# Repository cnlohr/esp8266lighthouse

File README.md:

# esp8266lighthouse

## Project log as of 5/28/17

So, general summary / log for esp8266lighthouse:   It works.  Surprisingly well.

1. If the base station is too close, it the signal quality gets pretty rough.   Too close = 0.8 meters or closer.  This may not be resolvable without a different opamp.  I don't know yet. 
2. There are some corner cases that will cause the ESP to freeze.  This is sad-making, however shouldn't be hard to troubleshoot.
3. The algorithm I'm using to determine frequency seems SLIGHTLY dependent on strength.  When pointed directly at the lighthouse and close, it seems to read slightly high (by about 10-15 kHz)  When at glancing angle or barely visible, it reads spot on.
4. The noise issue due to the ESP is really confusing to me.  Arbitrary moving something or switching power plugs around drastically changes the performance of the system.
5. The ESP8266 will draw ~14mA even in modem-sleep mode all the time if it is monitoring for a lighthouse.  This is sad.  I want to move to an FPGA, but because of the pinout on the ICE40 FPGAs and the fact they never put them in a reasonable package, PCBs for them cost about 10x what normal PCBs cost.
6. Though I can precisely tell frequencies, I cannot simultaneously decode pulses. Each pulse must have about 2uS between them in order to be treated as different pulses.   If we run lighthouses asynchronously, there will be some collisions.  They will need to be ignored.
7. The base stations CAN be run asynchronously and at different rates.  It seems to me that if the lighthouses are operating at the same frequency, they cannot disambiguate asynchronous pulses, but, we should be able to.

## Internal notes:

```
NOTES for transimpedence2/3
TESTS Performed with no C1, TSV992
Making R4 220k instead of 47k seeems to have little effect, but does make it worse.
Switching R1 for 47k just makes it appear drunk. There's some weird feedback thing going on.
    Like it tuned wrong or something.   Making it 10k quiets the signal a lot.
REMOVING C4 no apparent impact.

R5=10k, C5=10p -> R5=4.7k, C5=18p =>> Improvement.
Adding C1=1pF decreases amplitude a little bit but also cleans up edges.
Removing C6 seems to reduce amplitude slightly.

Far peak:
C1 none C6 none => .1238V noise, .998V Far Light
C1 none C6 1pF    => .1238V noise, .498V Far Light
C1 1pF  C6 none => .1135V noise, .358V Far Light
C1 1pF C6 1pF     => .087V Noise, .202V Far Light

Recommendation: Remove C6, C1.

Out of the following op amps...
TSH82, TSV992, AD8052, TSH22, TSH462,
TSV992 demolished.

Useful photodiodes:
PART / NOISE / FAR / Cost
PD70-01C/TR7:  .159 / .418 / .47
PD438C: .237 / .550 / .39
QSD2030F: .216 / .5363 / .30
BPW34/S-Z: .283 / .6345 /.497
PD15-216/TR8: UNUSABLE
VBPW34FAS: .175 / .815 / .778
VBPW34FASR: .2631 / .644 / .778
BPW34: .237 / .577 / .62
PD15-22C/TR8: Unworkable.
PD15-22B/TR8: Unworkable.
PD70-TR10: .2063 / .4024 / .41
BPW46: .247 / .968 / .61

Winners: BPW46, BPW34/S-Z, BPW34FAS + VBPW34FASR
Major Winners: BPW46/VBPW34FAS
```

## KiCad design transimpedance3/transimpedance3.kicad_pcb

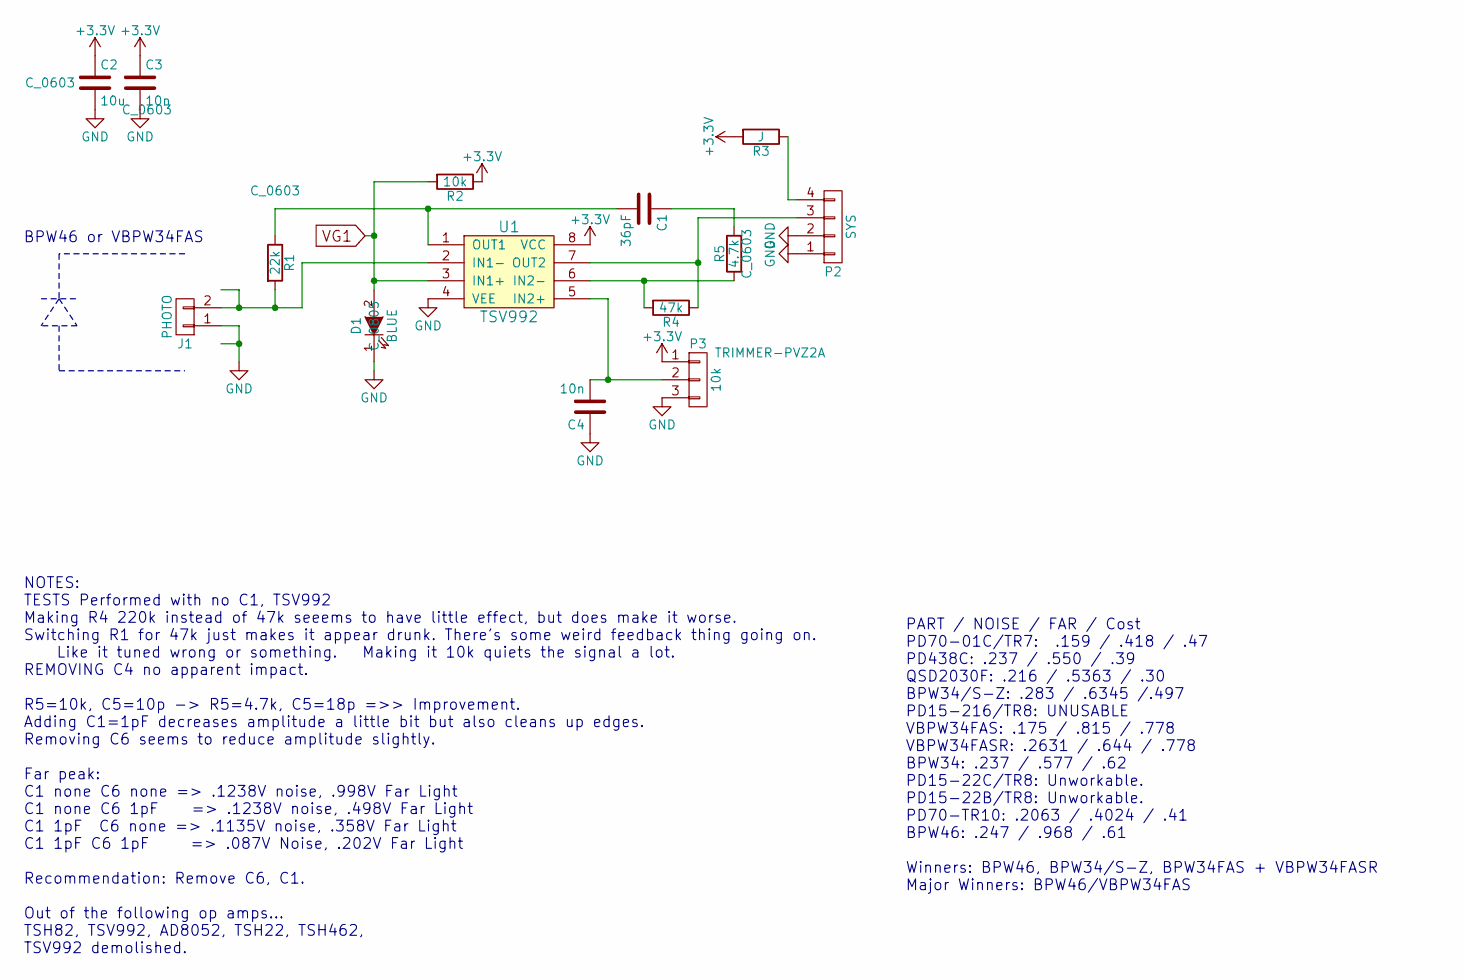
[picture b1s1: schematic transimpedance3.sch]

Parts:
C1: 36pF; C_0603
C2: 10u; C_0603
C3, C4: 10n; C_0603
D1: BLUE; C_0805
J1: PHOTO; Pin_Header_Straight_1x02_Pitch2.54mm
P2: SYS; TerminalBlock_Pheonix_MPT-2.54mm_4pol
P3: 10k; TRIMMER-PVZ2A
R1: 22k; C_0603
R2: 10k; C_0603
R3: J; C_0603
R4: 47k; C_0603
R5: 4.7k; C_0603
U1: TSV992; SSOP-8_2.95x2.8mm_Pitch0.65mm

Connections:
+3V3: C2.1, C3.1, P3.1, R2.1, R3.2, U1.8 (VCC)
GND: C2.2, C3.2, C4.1, D1.1 (K), J1.1, P2.1, P2.2, P3.3, U1.4 (VEE)
unnamed: C1.1, R5.2
unnamed: C1.2, R1.1, U1.1 (OUT1)
unnamed: C4.2, P3.2, U1.5 (IN2+)
unnamed: J1.2, R1.2, U1.2 (IN1-)
unnamed: P2.3, R4.1, U1.7 (OUT2)
unnamed: P2.4, R3.1
unnamed: R4.2, R5.1, U1.6 (IN2-)
VG1: D1.2 (A), R2.2, U1.3 (IN1+)

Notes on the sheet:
NOTES: TESTS Performed with no C1, TSV992 Making R4 220k instead of 47k seeems to have little effect, but does make it worse. Switching R1 for 47k just makes it appear drunk. There's some weird feedback thing going on. Like it tuned wrong or something. Making it 10k quiets the signal a lot. REMOVIN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
PART / NOISE / FAR / Cost PD70-01C/TR7: .159 / .418 / .47 PD438C: .237 / .550 / .39 QSD2030F: .216 / .5363 / .30 BPW34/S-Z: .283 / .6345 /.497 PD15-216/TR8: UNUSABLE VBPW34FAS: .175 / .815 / .778 VBPW34FASR: .2631 / .644 / .778 BPW34: .237 / .577 / .62 PD15-22C/TR8: Unworkable. PD15-22B/TR8: Unwork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
BPW46 or VBPW34FAS

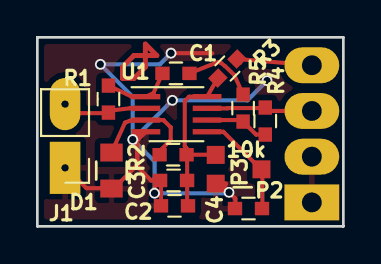
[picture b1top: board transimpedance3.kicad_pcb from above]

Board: 2 copper layers, 17.0 x 10.5 mm, 14 parts (0 on the bottom side), 10 nets.

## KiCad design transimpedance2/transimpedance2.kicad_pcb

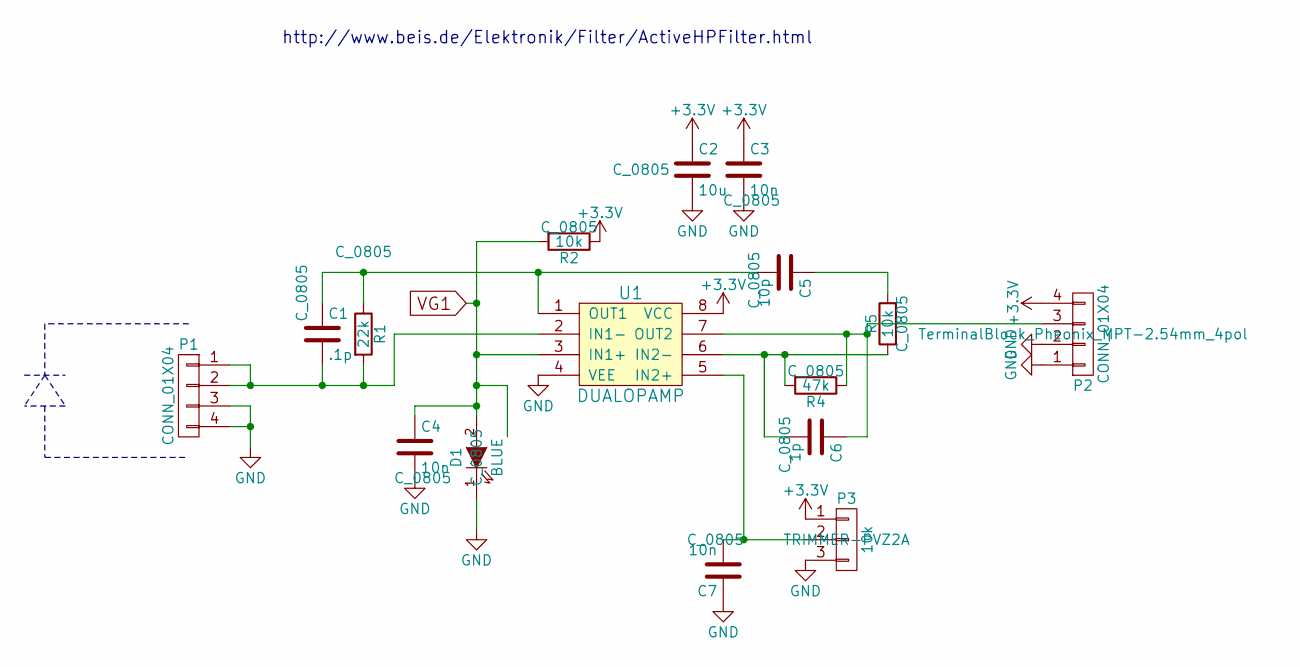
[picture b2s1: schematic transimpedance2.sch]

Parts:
C1: .1p; C_0805
C2: 10u; C_0805
C3, C4, C7: 10n; C_0805
C5: 10p; C_0805
C6: 1p; C_0805
D1: BLUE; C_0805
P1, P2: CONN_01X04; TerminalBlock_Pheonix_MPT-2.54mm_4pol
P3: 10k; TRIMMER-PVZ2A
R1: 22k; C_0805
R2, R5: 10k; C_0805
R4: 47k; C_0805
U1: DUALOPAMP; SOIC-8_3.9x4.9mm_Pitch1.27mm

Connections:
+3V3: C2.1, C3.1, P2.4, P3.1, R2.1, U1.8 (VCC)
GND: C2.2, C3.2, C4.2, C7.1, D1.1 (K), P1.3, P1.4, P2.1, P2.2, P3.3, U1.4 (VEE)
unnamed: C1.1, C5.2, R1.1, U1.1 (OUT1)
unnamed: C1.2, P1.1, P1.2, R1.2, U1.2 (IN1-)
unnamed: C5.1, R5.2
unnamed: C6.1, P2.3, R4.1, U1.7 (OUT2)
unnamed: C6.2, R4.2, R5.1, U1.6 (IN2-)
unnamed: C7.2, P3.2, U1.5 (IN2+)
VG1: C4.1, D1.2 (A), R2.2, U1.3 (IN1+)

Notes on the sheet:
http://www.beis.de/Elektronik/Filter/ActiveHPFilter.html

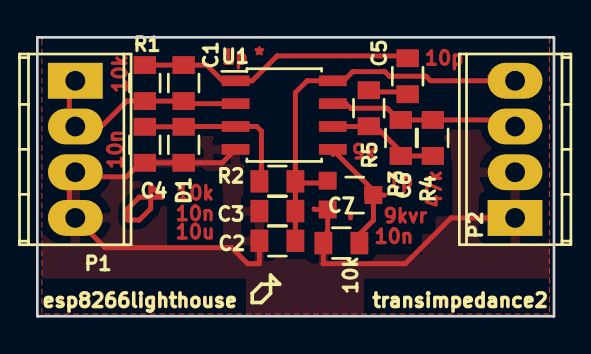
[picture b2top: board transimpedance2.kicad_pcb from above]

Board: 2 copper layers, 28.7 x 15.5 mm, 16 parts (0 on the bottom side), 9 nets.

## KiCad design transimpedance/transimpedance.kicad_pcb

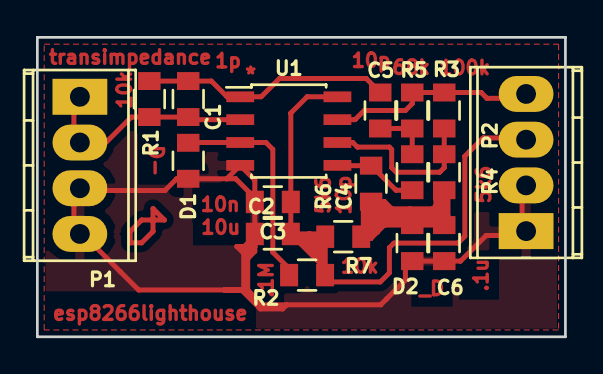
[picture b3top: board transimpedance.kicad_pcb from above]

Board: 2 copper layers, 29.3 x 16.6 mm, 18 parts (0 on the bottom side), 10 nets.

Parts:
C1, C4, C5: 10p; C_0805
C2: 10u; C_0805
C3: 10n; C_0805
C6: 100n; C_0805
D1, D2: BLUE; C_0805
P1, P2: CONN_01X04; TerminalBlock_Pheonix_MPT-2.54mm_4pol
R1, R7: 10k; C_0805
R2: 100k; C_0805
R3: 106k; C_0805
R4, R6: 5.6k; C_0805
R5: 68k; C_0805
U1: DUALOPAMP; SOIC-8_3.9x4.9mm_Pitch1.27mm

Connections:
+3V3: C2.1, C3.1, P2.3, R2.1, R7.1, U1.8
GND: C2.2, C3.2, C6.2, D1.1, D2.1, P1.3, P1.4, P2.1, P2.2, U1.4
unnamed: C1.1, C5.1, R1.1, U1.1
unnamed: C1.2, P1.1, P1.2, R1.2, U1.2
unnamed: C4.1, C5.2, R5.1
unnamed: C4.2, R6.2, U1.5
unnamed: P2.4, R3.2, R5.2, U1.7
unnamed: R3.1, R4.2, U1.6
VG1: D1.2, R2.2, U1.3
VGND: C6.1, D2.2, R4.1, R6.1, R7.2

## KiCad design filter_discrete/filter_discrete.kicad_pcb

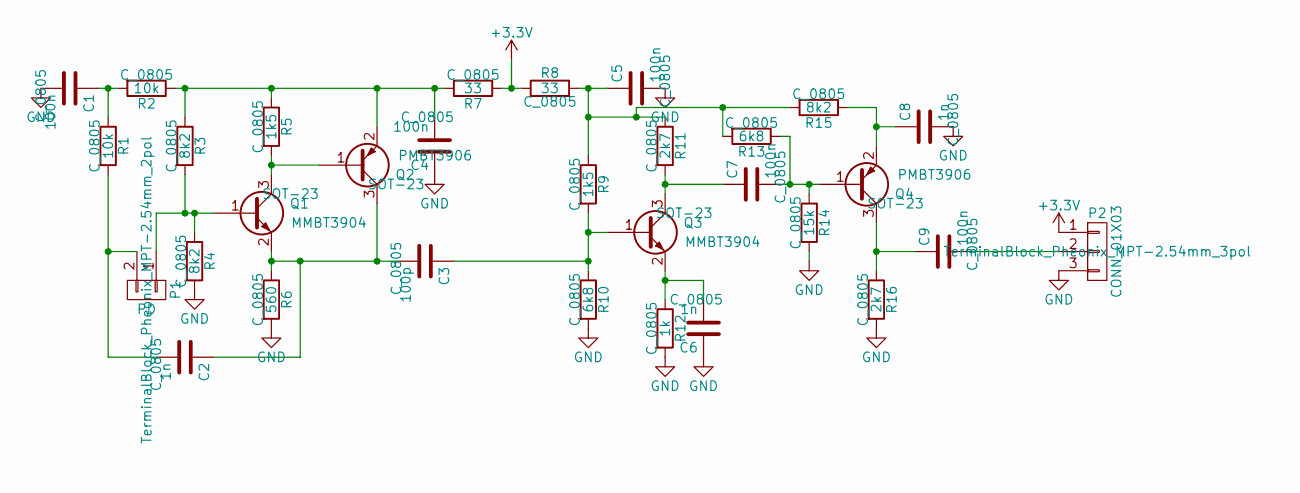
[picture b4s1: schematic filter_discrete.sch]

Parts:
C1, C4, C5, C7, C9: 100n; C_0805
C2, C6, C8: 1n; C_0805
C3: 100p; C_0805
P1: PD; TerminalBlock_Pheonix_MPT-2.54mm_2pol
P2: CONN_01X03; TerminalBlock_Pheonix_MPT-2.54mm_3pol
Q1, Q3: MMBT3904; SOT-23
Q2, Q4: PMBT3906; SOT-23
R1, R2: 10k; C_0805
R3, R4, R15: 8k2; C_0805
R5, R9: 1k5; C_0805
R6: 560; C_0805
R7, R8: 33; C_0805
R10, R13: 6k8; C_0805
R11, R16: 2k7; C_0805
R12: 1k; C_0805
R14: 15k; C_0805

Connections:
+3V3: P2.1, R7.1, R8.1
GND: C1.2, C4.1, C5.2, C6.1, C8.2, P2.3, R4.2, R6.2, R10.2, R12.2, R14.2, R16.2
unnamed: C1.1, R1.1, R2.2
unnamed: C2.1, C3.2, Q1.2 (E), Q2.3 (C), R6.1
unnamed: C2.2, P1.2, R1.2
unnamed: C3.1, Q3.1 (B), R9.2, R10.1
unnamed: C4.2, Q2.2 (E), R2.1, R3.1, R5.1, R7.2
unnamed: C5.1, R8.2, R9.1, R11.1, R13.2, R15.2
unnamed: C6.2, Q3.2 (E), R12.1
unnamed: C7.1, Q3.3 (C), R11.2
unnamed: C7.2, Q4.1 (B), R13.1, R14.1
unnamed: C8.1, Q4.2 (E), R15.1
unnamed: C9.1, Q4.3 (C), R16.1
unnamed: C9.2, P2.2
unnamed: P1.1, Q1.1 (B), R3.2, R4.1
unnamed: Q1.3 (C), Q2.1 (B), R5.2

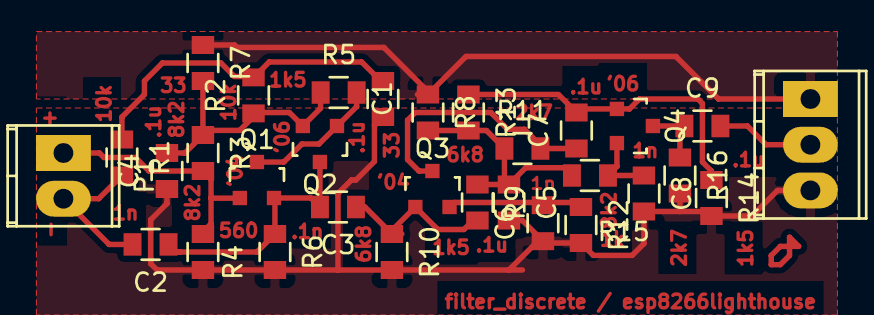
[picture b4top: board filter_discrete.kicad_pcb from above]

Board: 2 copper layers, 31 parts (0 on the bottom side), 16 nets.

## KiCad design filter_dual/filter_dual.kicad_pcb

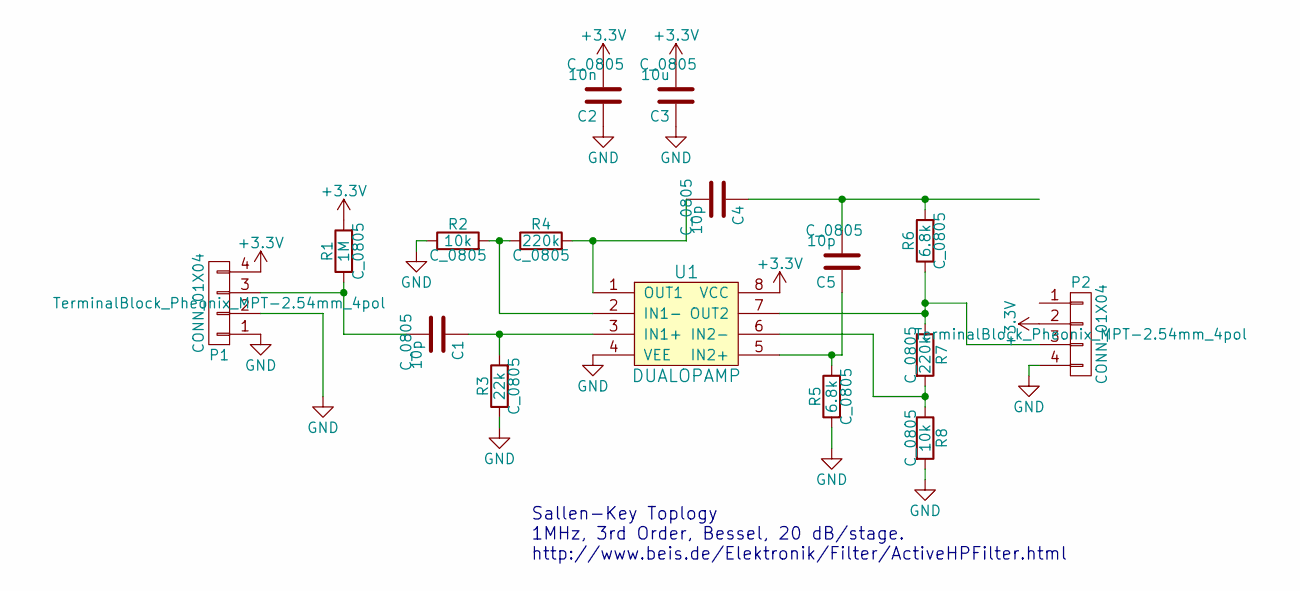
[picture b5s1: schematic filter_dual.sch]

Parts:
C1, C4, C5: 10p; C_0805
C2: 10n; C_0805
C3: 10u; C_0805
P1, P2: CONN_01X04; TerminalBlock_Pheonix_MPT-2.54mm_4pol
R1: 1M; C_0805
R2, R8: 10k; C_0805
R3: 22k; C_0805
R4, R7: 220k; C_0805
R5, R6: 6.8k; C_0805
U1: DUALOPAMP; SOIC-8_3.9x4.9mm_Pitch1.27mm

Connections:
+3V3: C2.2, C3.2, P1.4, P2.2, R1.2, U1.8 (VCC)
GND: C2.1, C3.1, P1.1, P1.2, P2.4, R2.1, R3.1, R5.1, R8.2, U1.4 (VEE)
unnamed: C1.1, R3.2, U1.3 (IN1+)
unnamed: C1.2, P1.3, R1.1
unnamed: C4.1, C5.2, R6.2
unnamed: C4.2, R4.2, U1.1 (OUT1)
unnamed: C5.1, R5.2, U1.5 (IN2+)
unnamed: P2.3, R6.1, R7.1, U1.7 (OUT2)
unnamed: R2.2, R4.1, U1.2 (IN1-)
unnamed: R7.2, R8.1, U1.6 (IN2-)

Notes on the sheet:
Sallen-Key Toplogy 1MHz, 3rd Order, Bessel, 20 dB/stage. http://www.beis.de/Elektronik/Filter/ActiveHPFilter.html

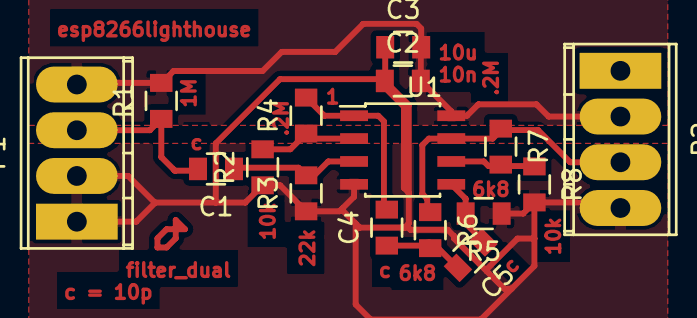
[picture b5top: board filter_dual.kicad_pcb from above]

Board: 2 copper layers, 16 parts (0 on the bottom side), 10 nets.

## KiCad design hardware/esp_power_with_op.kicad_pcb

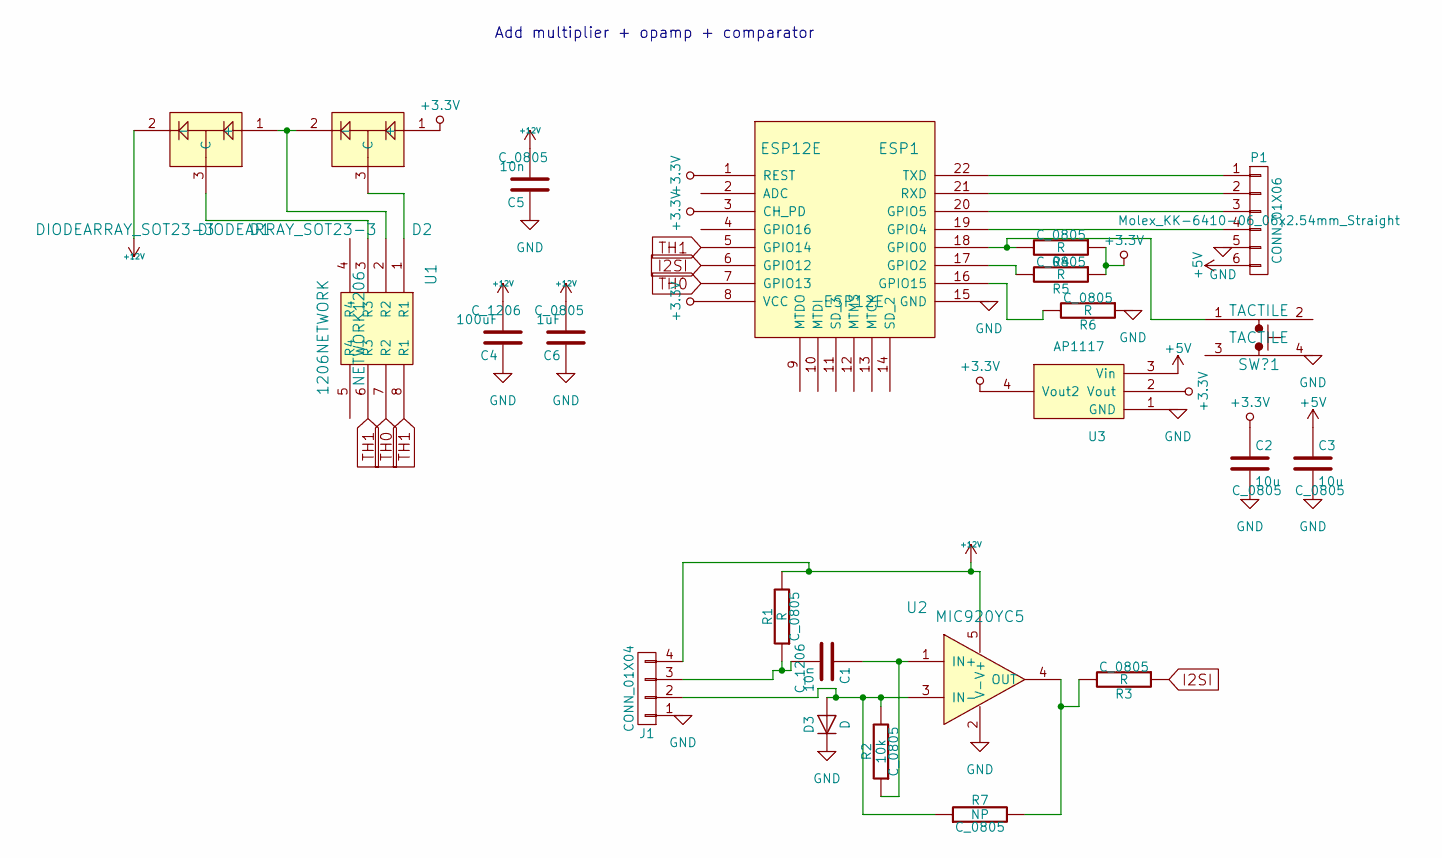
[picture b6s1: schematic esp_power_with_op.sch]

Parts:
C1: 10n; C_1206
C2, C3: 10u; C_0805
C4: 100uF; C_1206
C5: 10n; C_0805
C6: 1uF; C_0805
D1, D2: DIODEARRAY_SOT23-3; SOT-23
D3: D; C_1206
ESP1: ESP12E
J1: CONN_01X04; Molex_KK-6410-04_04x2.54mm_Straight
P1: CONN_01X06; Molex_KK-6410-06_06x2.54mm_Straight
R1, R3, R4, R5, R6: R; C_0805
R2: 10k; C_0805
R7: NP; C_0805
SW?1: TACTILE
U1: 1206NETWORK; NETWORK1206
U2: MIC920YC5; SOT-353_SC-70-5
U3: AP1117; SOT-223

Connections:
+3.3V: C2.1, D2.1 (+), ESP1.1 (REST), ESP1.3 (CH_PD), ESP1.8 (VCC), R4.1, R5.1, U3.2 (Vout), U3.4 (Vout2)
+5V: C3.1, P1.6, U3.3 (Vin)
+12V: C4.2, C5.2, C6.2, D1.2 (-), J1.4, R1.2, U2.5 (V+)
GND: C2.2, C3.2, C4.1, C5.1, C6.1, D3.1 (K), ESP1.15 (GND), J1.1, P1.5, R6.1, SW?1.4, U2.2 (V-), U3.1 (GND)
I2SI: ESP1.6 (GPIO12), R3.1
unnamed: C1.1, R2.1, U2.1 (IN+)
unnamed: C1.2, J1.3, R1.1
unnamed: D1.1 (+), D2.2 (-), U1.2 (R2)
unnamed: D1.3 (C), U1.3 (R3)
unnamed: D2.3 (C), U1.1 (R1)
unnamed: D3.2 (A), J1.2, R2.2, R7.1, U2.3 (IN-)
unnamed: ESP1.16 (GPIO15), R6.2
unnamed: ESP1.17 (GPIO2), R5.2
unnamed: ESP1.18 (GPIO0), R4.2, SW?1.1
unnamed: ESP1.19 (GPIO4), P1.4
unnamed: ESP1.20 (GPIO5), P1.3
unnamed: ESP1.21 (RXD), P1.2
unnamed: ESP1.22 (TXD), P1.1
unnamed: R3.2, R7.2, U2.4 (OUT)
TH0: ESP1.7 (GPIO13), U1.7 (R2)
TH1: ESP1.5 (GPIO14), U1.6 (R3), U1.8 (R1)

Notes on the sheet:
Add multiplier + opamp + comparator

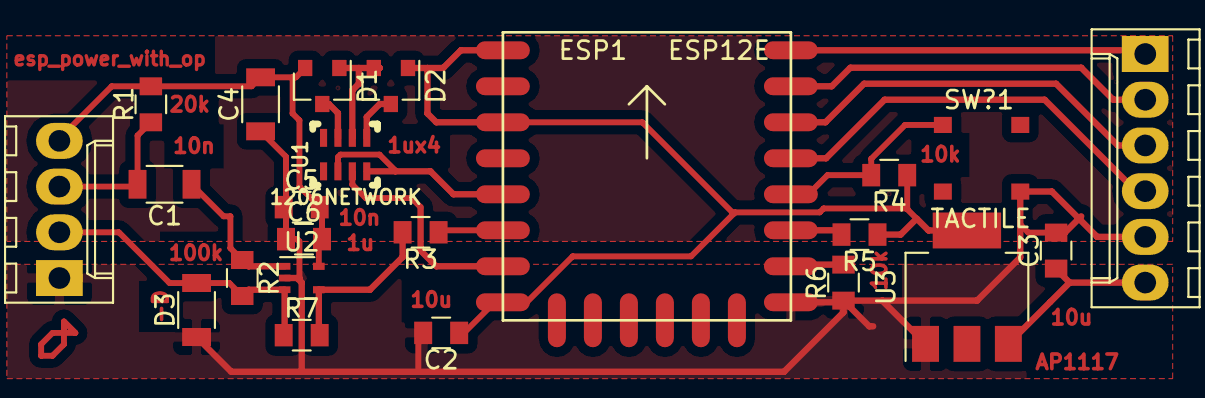
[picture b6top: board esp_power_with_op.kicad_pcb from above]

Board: 2 copper layers, 23 parts (0 on the bottom side), 21 nets.

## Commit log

2017-03-26 Add all parts to this repo.
2017-03-26 remove chage pump etc
2017-03-26 Update - swapping files aroundo
2017-03-30 Add other filters.
2017-03-30 add updated files
2017-03-30 update lighthouse designs
2017-03-31 update transimpedence filter.
2017-04-04 update with transimpedance 2
2017-05-01 update the transimpedance esign.
2017-05-11 update transimpedance3
2017-05-11 update tia3
2017-05-12 Update all designs with newest to fab.
2017-05-12 update schematic
2017-05-15 Update the esp8266 lighthouse code to allow browser-interaction.
2017-05-15 Update firmware, and improve performance.
2017-05-15 cleanup styles on website, plus, remove the I2S TX engine. Hopefully this will relieve some DMA contention.
2017-05-16 bump submodule
2017-05-16 added missing unit
    Browsers only allow this in quirks mode and you shouldn't rely on that.
    I know it's nothing major, just noticed it in the steam ^^
2017-05-17 Update to a binary websockets. Improve usage
2017-05-18 Update processing systems
2017-05-18 Closing in on a solution!!!
2017-05-18 Working successfully with web gui (Also update project for kicad)
2017-05-18 Update with fully functional tracking code and sending over UDP (though there is some debt that need be handled)
2017-05-18 Issues with the DMA buffer system in the ESP. Must be fixed. Other than that, getting very close.
2017-05-18 fix bug with bad scoping.
2017-05-19 Getting very close. A few buffer underruns and I need to stop using UDP (for now!)
2017-05-19 oops, shouldn't have deleted that code from the custom controller
2017-05-27 Transition over to TCP for main transport mechanism.
2017-05-27 Fix bug in FDM decoding for 1.2 MHz specifically.
2017-05-30 Update processing, etc. to include transition values.
2017-05-30 Add minimize error
2017-05-31 Fix crash in lighthouse decode with possible negative indexes.
2017-07-12 bump revision
